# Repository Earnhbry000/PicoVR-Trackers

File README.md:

# PicoVR-Trackers
A Collection of trackers &amp; Designs as well as documentation for PicoVR Trackers

# (Documentation Coming Soon)

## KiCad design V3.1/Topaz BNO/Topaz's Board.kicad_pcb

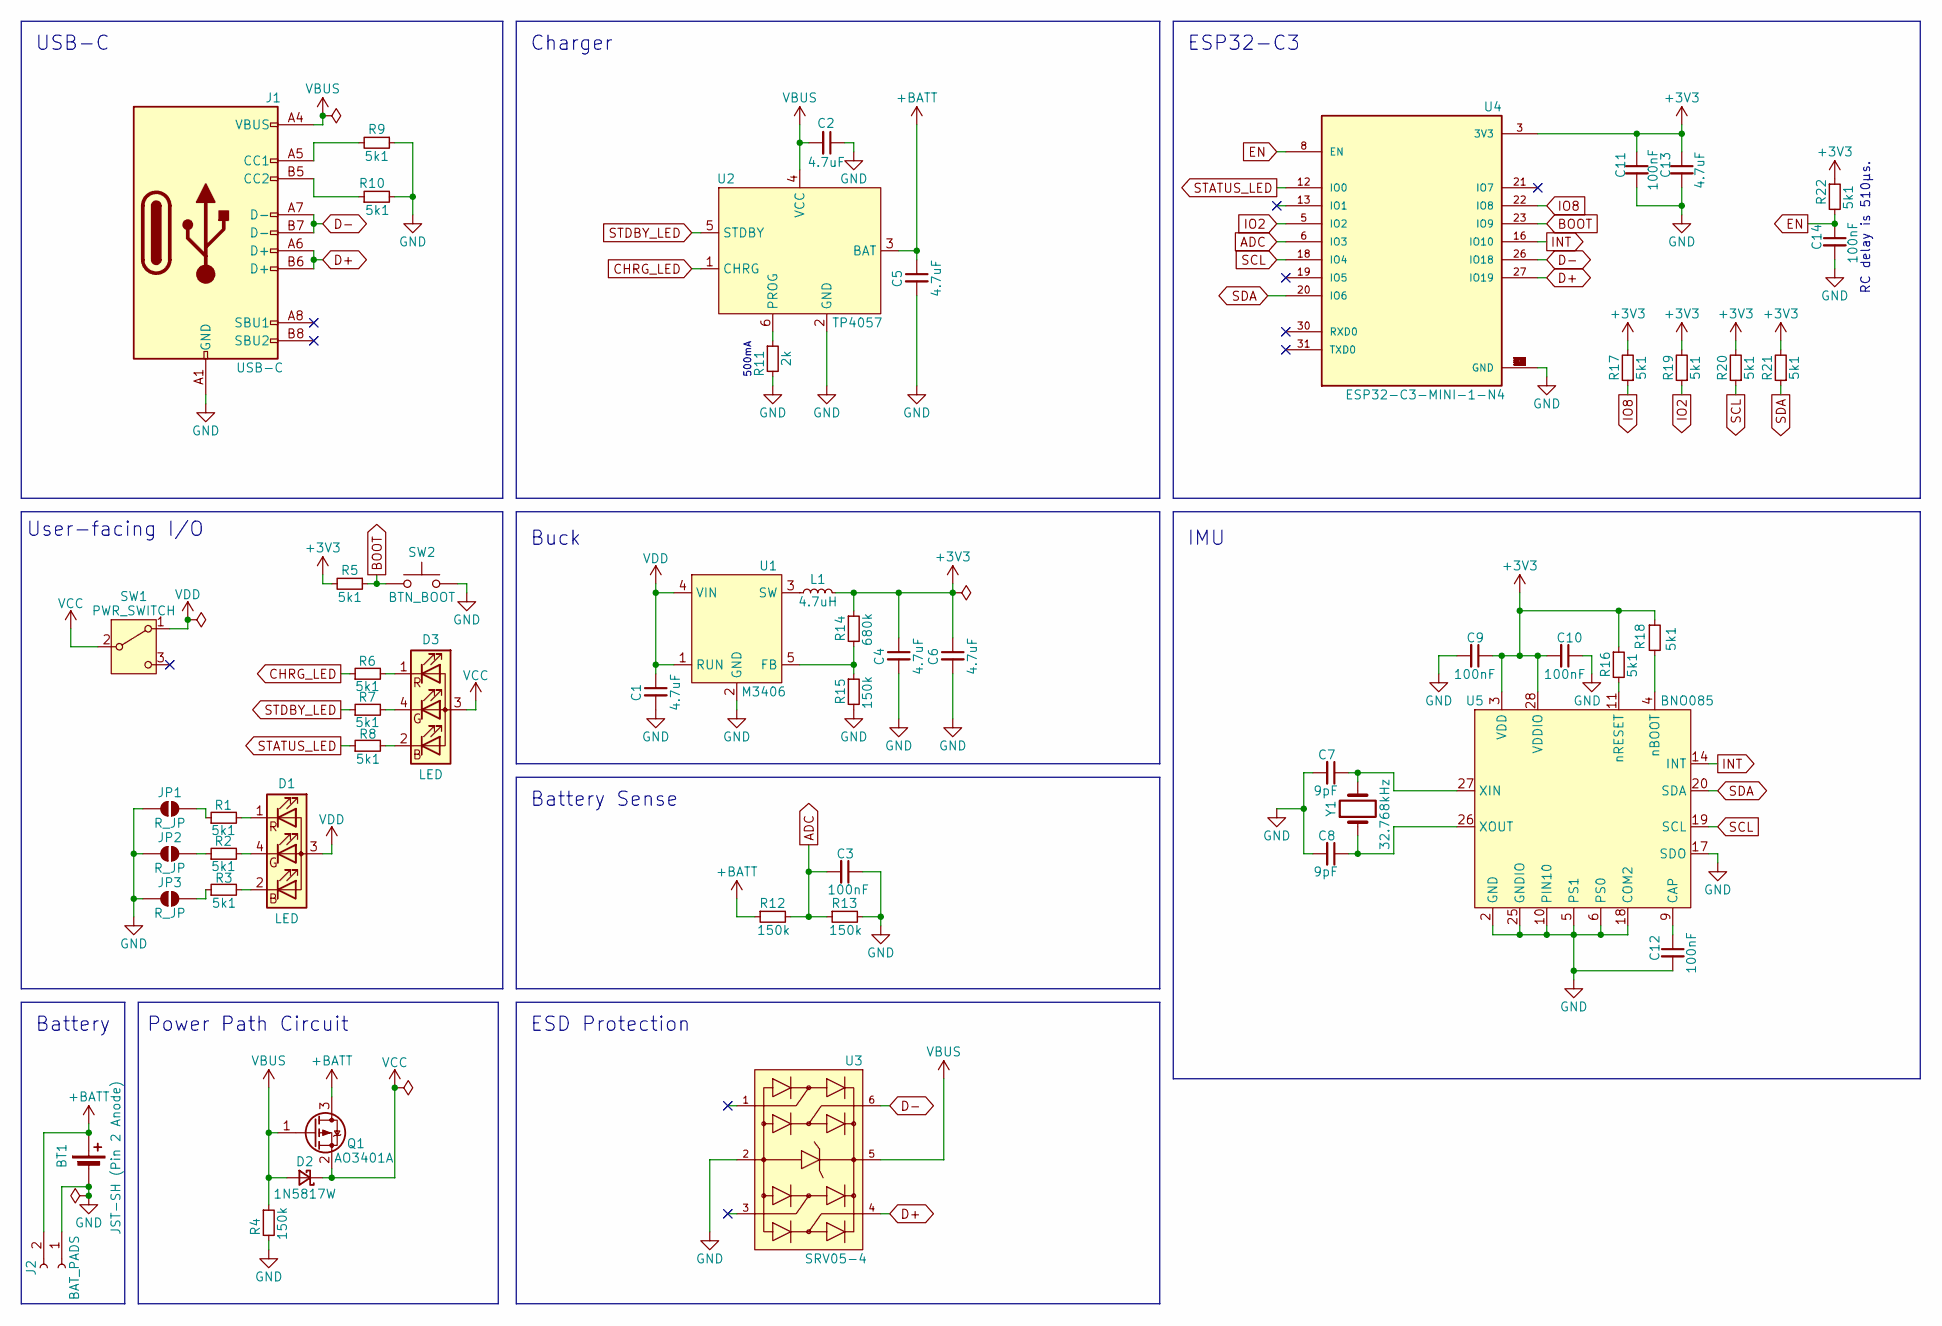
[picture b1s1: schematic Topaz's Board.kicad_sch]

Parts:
BT1: JST-SH (Pin 2 Anode); JST_SH_SM02B-SRSS-TB_1x02-1MP_P1.00mm_Horizontal; MPN C160402
C1, C2, C4, C5, C6, C13: 4.7uF; C_0603_1608Metric; MPN C19666
C3, C9, C10, C11, C12, C14: 100nF; C_0603_1608Metric; MPN C14663
C7, C8: 9pF; C_0603_1608Metric; MPN C282076
D1, D3: LED; LED-ARRAY-SMD_4P-L2.1-W2.1-TL_NH-B2020RGBA; MPN C2874116
D2: 1N5817W; D_SOD-123; MPN C2828419
J1: USB-C; USB_C_Receptacle_GCT_USB4105-xx-A_16P_TopMnt_Horizontal; MPN C2765186
J2: BAT_PADS; PinHeader_1x02_P2.54mm_Vertical; MPN N/A
JP1, JP2, JP3: R_JP; SolderJumper-2_P1.3mm_Open_TrianglePad1.0x1.5mm; MPN N/A
L1: 4.7uH; L_0806_2012Metric; MPN C98335
Q1: AO3401A; SOT-23; MPN C6575062
R1, R2, R3, R5, R6, R7, R8, R9, R10, R16, R17, R18, R19, R20, R21, R22: 5k1; R_0603_1608Metric; MPN C23186
R4, R12, R13, R15: 150k; R_0603_1608Metric; MPN C22807
R11: 2k; R_0603_1608Metric; MPN C22975
R14: 680k; R_0603_1608Metric; MPN C25822
SW1: PWR_SWITCH; THTSwitch; MPN C431548
SW2: BTN_BOOT; NewCheapoButton; MPN C139797
U1: M3406; SOT-23-5; MPN C83224
U2: TP4057; SOT-23-6; MPN C725791
U3: SRV05-4; SOT-23-6; MPN C2836319
U4: ESP32-C3-MINI-1-N4; ESP32-C3-MINI-1; MPN C2838502
U5: BNO085; LGA-28_5.2x3.8mm_P0.5mm; MPN C5189642
Y1: 32.768kHz; Crystal_SMD_3215-2Pin_3.2x1.5mm; MPN C479190

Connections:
+3V3: C4.1, C6.1, C9.1, C10.2, C11.1, C13.1, L1.2, R5.2, R14.1, R16.1, R17.2, R18.1, R19.2, R20.2, R21.2, R22.1, U4.3 (3V3), U5.3 (VDD), U5.28 (VDDIO)
+BATT: BT1.1 (+), C5.1, J2.2, Q1.3 (D), R12.1, U2.3 (BAT)
ADC: C3.2, R12.2, R13.1, U4.6 (IO3)
BOOT: R5.1, SW2.1, U4.23 (IO9)
CHRG_LED: R6.1, U2.1 (CHRG)
D+: J1.A6 (D+), J1.B6 (D+), U3.4, U4.27 (IO19)
D-: J1.A7 (D-), J1.B7 (D-), U3.6, U4.26 (IO18)
EN: C14.1, R22.2, U4.8 (EN)
GND: BT1.2 (-), C1.2, C2.1, C3.1, C4.2, C5.2, C6.2, C7.2, C8.2, C9.2, C10.1, C11.2, C12.2, C13.2, C14.2, J1.A1 (GND), J2.1, JP1.1 (A), JP2.1 (A), JP3.1 (A), R4.2, R9.1, R10.2, R11.2, R13.2, R15.2, SW2.2, U1.2 (GND), U2.2 (GND), U3.2, U4.1 (GND), U4.2 (GND), U4.11 (GND), U4.14 (GND), U4.36 (GND), U4.37 (GND), U4.38 (GND), U4.39 (GND), U4.40 (GND), U4.41 (GND), U4.42 (GND), U4.43 (GND), U4.44 (GND), U4.45 (GND), U4.46 (GND), U4.47 (GND), U4.48 (GND), U4.49 (GND), U4.50 (GND), U4.51 (GND), U4.52 (GND), U4.53 (GND), U5.2 (GND), U5.5 (PS1), U5.6 (PS0), U5.10 (PIN10), U5.17 (SDO), U5.18 (COM2), U5.25 (GNDIO)
INT: U4.16 (IO10), U5.14 (INT)
IO2: R19.1, U4.5 (IO2)
IO8: R17.1, U4.22 (IO8)
unnamed: D1.2 (BK), R3.2
unnamed: D1.4 (GK), R2.2
unnamed: D1.1 (RK), R1.2
unnamed: D3.2 (BK), R8.2
unnamed: D3.4 (GK), R7.2
unnamed: D3.1 (RK), R6.2
unnamed: J1.A5 (CC1), R9.2
unnamed: J1.B5 (CC2), R10.1
unnamed: JP1.2 (B), R1.1
unnamed: JP2.2 (B), R2.1
unnamed: JP3.2 (B), R3.1
unnamed: R14.2, R15.1, U1.5 (FB)
unnamed: L1.1, U1.3 (SW)
unnamed: R11.1, U2.6 (PROG)
unnamed: C12.1, U5.9 (CAP)
unnamed: C7.1, U5.27 (XIN), Y1.2
unnamed: C8.1, U5.26 (XOUT), Y1.1
unnamed: R18.2, U5.4 (nBOOT)
unnamed: R16.2, U5.11 (nRESET)
SCL: R20.1, U4.18 (IO4), U5.19 (SCL)
SDA: R21.1, U4.20 (IO6), U5.20 (SDA)
STATUS_LED: R8.1, U4.12 (IO0)
STDBY_LED: R7.1, U2.5 (STDBY)
VBUS: C2.2, D2.2 (A), J1.A4 (VBUS), Q1.1 (G), R4.1, U2.4 (VCC), U3.5
VCC: D2.1 (K), D3.3 (A), Q1.2 (S), SW1.2 (B)
VDD: C1.1, D1.3 (A), SW1.1 (A), U1.1 (RUN), U1.4 (VIN)

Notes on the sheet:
USB-C
RC delay is 510µs.
Buck
User-facing I/O
ESP32-C3
500mA
ESD Protection
Charger
Power Path Circuit
Battery Sense
Battery
IMU

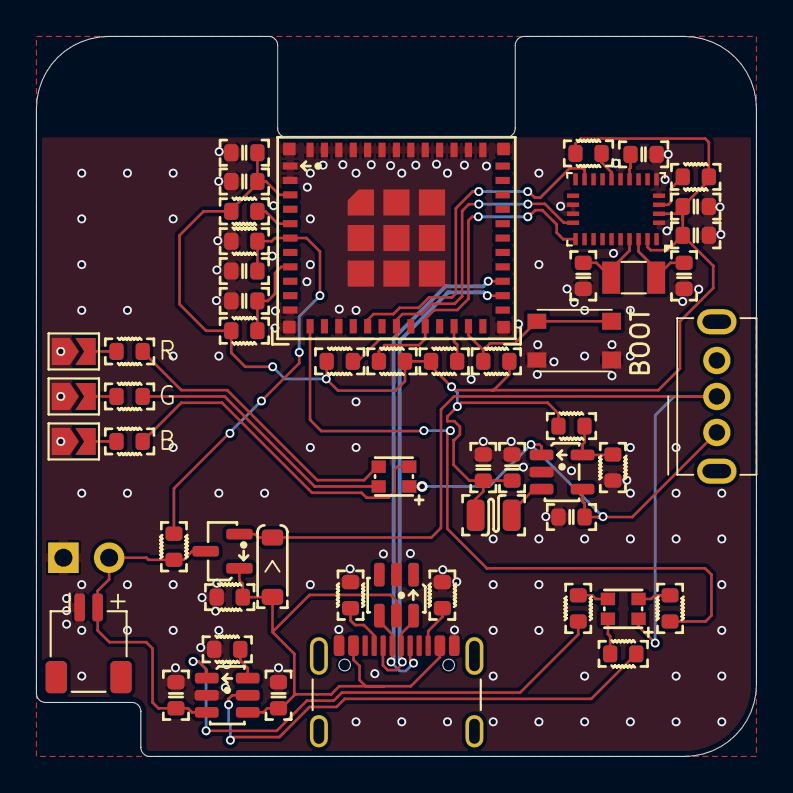
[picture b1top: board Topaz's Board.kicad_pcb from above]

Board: 2 copper layers, 40.0 x 40.0 mm, 55 parts (0 on the bottom side), 38 nets.

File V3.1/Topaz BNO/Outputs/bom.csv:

Designator,Footprint,Quantity,Value,LCSC Part #
BT1,JST_SH_SM02B-SRSS-TB_1x02-1MP_P1.00mm_Horizontal,1,JST-SH (Pin 2 Anode),C160402
"C1, C13, C2, C4, C5, C6",0603,6,4.7uF,C19666
"C10, C11, C12, C14, C3, C9",0603,6,100nF,C14663
"C7, C8",0603,2,9pF,C282076
"D1, D3",LED-ARRAY-SMD_4P-L2.1-W2.1-TL_NH-B2020RGBA,2,LED,C2874116
D2,D_SOD-123,1,1N5817W,C2828419
J1,USB_C_Receptacle_GCT_USB4105-xx-A_16P_TopMnt_Horizontal,1,USB-C,C2765186
L1,0806,1,4.7uH,C98335
Q1,SOT-23,1,AO3401A,C6575062
"R1, R10, R16, R17, R18, R19, R2, R20, R21, R22, R3, R5, R6, R7, R8, R9",0603,16,5k1,C23186
R11,0603,1,2k,C22975
"R12, R13, R15, R4",0603,4,150k,C22807
R14,0603,1,680k,C25822
SW1,THTSwitch,1,PWR_SWITCH,C431548
SW2,NewCheapoButton,1,BTN_BOOT,C139797
U1,SOT-23-5,1,M3406,C83224
U2,SOT-23-6,1,TP4057,C725791
U3,SOT-23-6,1,SRV05-4,C2836319
U4,ESP32-C3-MINI-1,1,ESP32-C3-MINI-1-N4,C2838502
U5,LGA-28_5.2x3.8mm_P0.5mm,1,BNO085,C5189642
Y1,Crystal_SMD_3215-2Pin_3.2x1.5mm,1,32.768kHz,C479190

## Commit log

2025-01-11 V2 Production File
2025-01-11 Create placeholder
2025-01-11 V2 Production File in right folder
2025-01-11 Autodesk 123D Design Case Files for V2
